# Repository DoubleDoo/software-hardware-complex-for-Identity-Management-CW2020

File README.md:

# software-hardware-complex-for-Identity-Management
software-hardware complex for Identity Management - course work 2019-2020

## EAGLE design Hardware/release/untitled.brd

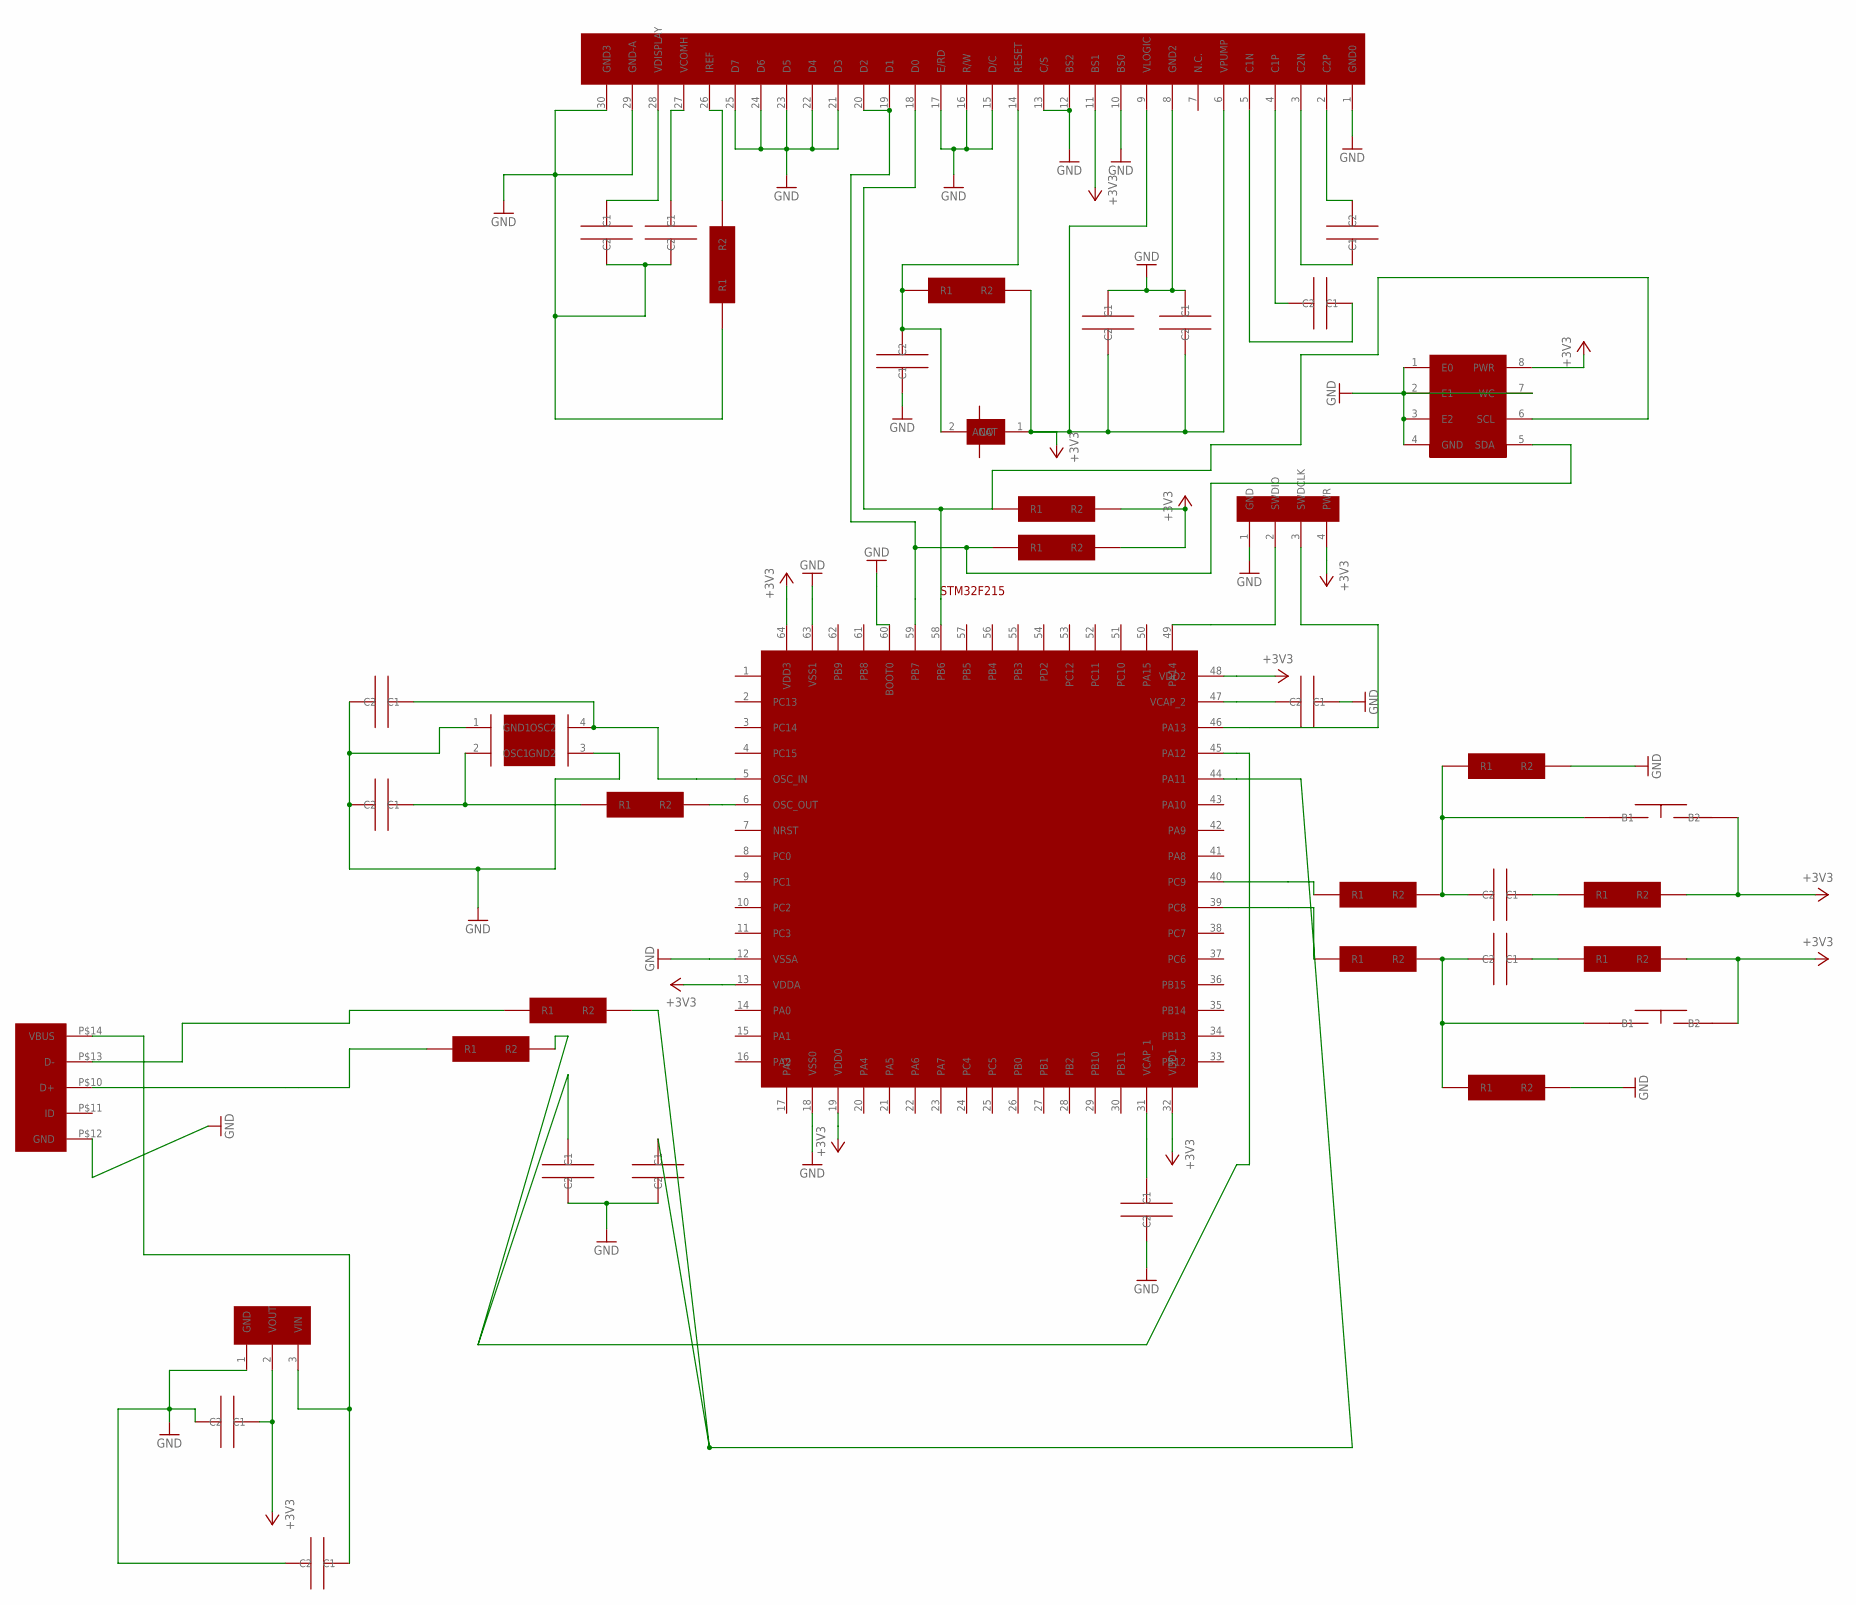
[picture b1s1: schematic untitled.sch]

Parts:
C3: 10мкф; 0805
C4: 22мкф; 0805
C10, C11: 100нф; 0805
C28, C29: 8пф; 0805
C30, C31: 47пф; 0805
C36, C37, C46: 2.2мкф; 0805
C39, C40, C41, C42: 1мкф; 0805
C44, C47: 4.7мкф; 0805
R2, R3: 330; 0805
R6, R7: 100; 0805
R8, R9: 10к; 0805
R14, R15: 220k; 0805
R32: 820; 0805
R33, R34: 22; 0805
R43: 4.7к; 0805
R48: 910к; 0805
U$1: STM32F215RESTM32; QFP50P1300X1300X120-64N
U$2: AMS1117; SOT229P729X180-4N
U$3: I2CMEMORY; SOIC127P600X175-8N
U$4: USBUSBT; USBT
U$5: SWDSWDD; HDRV4W64P254_1X4_1016X508X838B
U$18, U$19: BUTTON
U$26: NX2520SA
U$38: SSD1306
U$45: ESD

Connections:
+3V3: C4.2 (C2), C41.1 (C1), C42.1 (C1), R6.2 (R2), R7.2 (R2), R8.2 (R2), R9.2 (R2), R43.2 (R2), U$1.13 (VDDA), U$1.19 (VDD0), U$1.32 (VDD1), U$1.48 (VDD2), U$1.64 (VDD3), U$2.2 (VOUT), U$3.8 (PWR), U$5.4 (PWR), U$18.2 (B2), U$19.2 (B2), U$38.6 (VPUMP), U$38.9 (VLOGIC), U$38.11 (BS1), U$45.1 (ANO)
GND: C3.1 (C1), C4.1 (C1), C28.1 (C1), C29.1 (C1), C30.1 (C1), C31.1 (C1), C36.1 (C1), C37.2 (C2), C41.2 (C2), C42.2 (C2), C44.2 (C2), C46.1 (C1), C47.1 (C1), R14.2 (R2), R15.2 (R2), R48.1 (R1), U$1.12 (VSSA), U$1.18 (VSS0), U$1.60 (BOOT0), U$1.63 (VSS1), U$2.1 (GND), U$3.1 (E0), U$3.2 (E1), U$3.3 (E2), U$3.4 (GND), U$3.7 (WC), U$4.P$12 (GND), U$5.1 (GND), U$26.1 (GND1), U$26.3 (GND2), U$38.1 (GND0), U$38.8 (GND2), U$38.10 (BS0), U$38.12 (BS2), U$38.13 (C/S), U$38.15 (D/C), U$38.16 (R/W), U$38.17 (E/RD), U$38.21 (D3), U$38.22 (D4), U$38.23 (D5), U$38.24 (D6), U$38.25 (D7), U$38.29 (GND-A), U$38.30 (GND3)
unnamed: C30.2 (C2), R33.2 (R2), U$1.44 (PA11)
unnamed: C11.1 (C1), R3.2 (R2), R15.1 (R1), U$19.1 (B1)
unnamed: C11.2 (C2), R7.1 (R1)
unnamed: C10.1 (C1), R2.2 (R2), R14.1 (R1), U$18.1 (B1)
unnamed: C10.2 (C2), R6.1 (R1)
unnamed: R32.2 (R2), U$1.6 (OSC_OUT)
unnamed: C28.2 (C2), U$1.5 (OSC_IN), U$26.4 (OSC2)
unnamed: C29.2 (C2), R32.1 (R1), U$26.2 (OSC1)
unnamed: C31.2 (C2), R34.2 (R2), U$1.45 (PA12)
unnamed: C36.2 (C2), U$1.31 (VCAP_1)
unnamed: R33.1 (R1), U$4.P$13 (D-)
unnamed: R34.1 (R1), U$4.P$10 (D+)
unnamed: C37.1 (C1), U$1.47 (VCAP_2)
unnamed: R3.1 (R1), U$1.39 (PC8)
unnamed: R2.1 (R1), U$1.40 (PC9)
unnamed: C39.1 (C1), U$38.2 (C2P)
unnamed: C39.2 (C2), U$38.3 (C2N)
unnamed: C40.1 (C1), U$38.4 (C1P)
unnamed: C40.2 (C2), U$38.5 (C1N)
unnamed: C44.1 (C1), R43.1 (R1), U$38.14 (RESET), U$45.2 (CAT)
unnamed: C3.2 (C2), U$2.3 (VIN), U$4.P$14 (VBUS)
unnamed: R48.2 (R2), U$38.26 (IREF)
unnamed: C47.2 (C2), U$38.27 (VCOMH)
unnamed: C46.2 (C2), U$38.28 (VDISPLAY)
unnamed: R9.1 (R1), U$1.59 (PB7), U$3.5 (SDA), U$38.19 (D1), U$38.20 (D2)
unnamed: R8.1 (R1), U$1.58 (PB6), U$3.6 (SCL), U$38.18 (D0)
unnamed: U$1.49 (PA14), U$5.2 (SWDIO)
unnamed: U$1.46 (PA13), U$5.3 (SWDCLK)
VBAT: U$1.1 (VBAT)

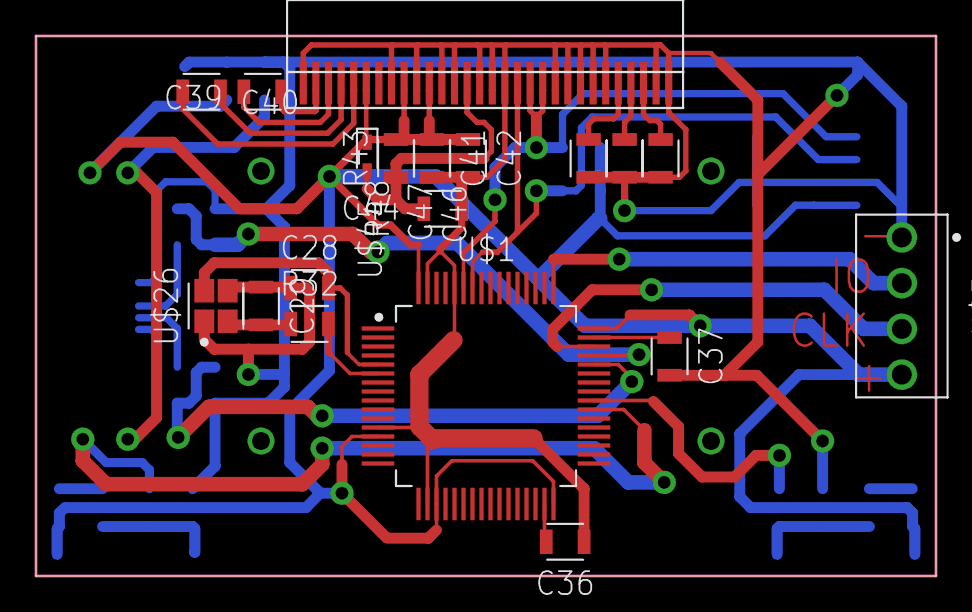
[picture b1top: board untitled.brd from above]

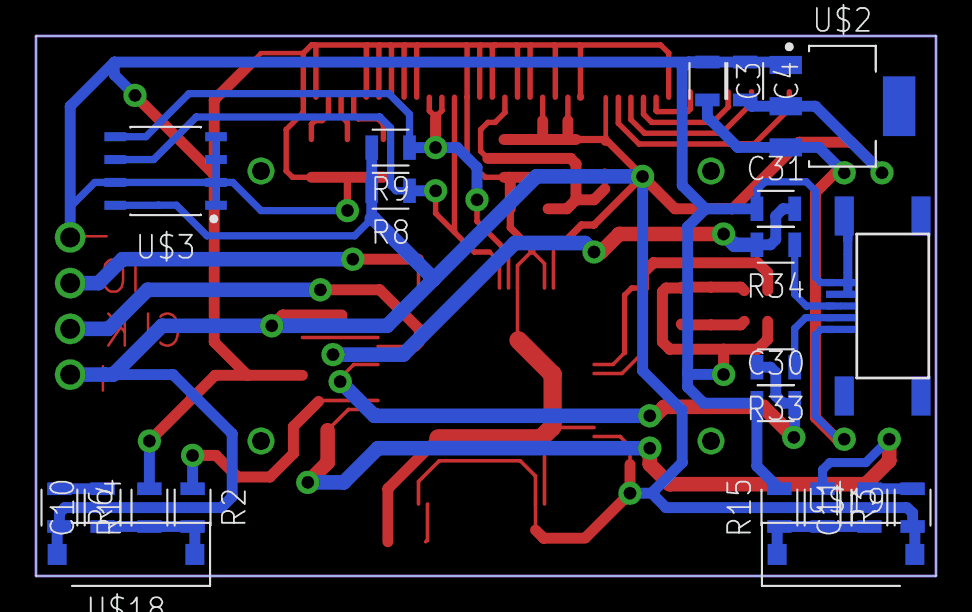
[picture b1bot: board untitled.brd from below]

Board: 2 copper layers, 50.0 x 30.0 mm, 40 parts (21 on the bottom side), 30 nets.

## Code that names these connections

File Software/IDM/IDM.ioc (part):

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Mcu.Name=STM32F215R(E-G)Tx
Mcu.Package=LQFP64
Mcu.UserName=STM32F215RETx
PA11.Mode=Device_Only
PA11.Signal=USB_OTG_FS_DM
PA12.Mode=Device_Only
PA12.Signal=USB_OTG_FS_DP
PB6.Mode=I2C
PB6.Signal=I2C1_SCL
PB7.Mode=I2C
PB7.Signal=I2C1_SDA
PC8.Signal=GPXTI8
PC9.Signal=GPXTI9
PH0-OSC_IN.Mode=HSE-External-Oscillator
PH0-OSC_IN.Signal=RCC_OSC_IN
PH1-OSC_OUT.Mode=HSE-External-Oscillator
PH1-OSC_OUT.Signal=RCC_OSC_OUT
RCC.HSE_VALUE=24000000
RCC.SYSCLKFreq_VALUE=24000000
RCC.SYSCLKSource=RCC_SYSCLKSOURCE_HSE
board=custom

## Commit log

2019-11-03 TP development
2020-03-04 circuit updated
2020-03-24 circuit updated, add software project
2020-04-04 Add final circuit, create code project, add case model
2020-04-13 Add memory functions, autorization data funk
2020-04-15 add docs prototypes, some code
2020-04-16 fixes
